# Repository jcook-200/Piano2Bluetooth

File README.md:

# Piano2Bluetooth
A hardware and software project to let a digital piano connect to Bluetooth headphones.

## Scructure

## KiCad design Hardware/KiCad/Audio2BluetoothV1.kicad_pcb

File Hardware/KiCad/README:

These are the kicad design files

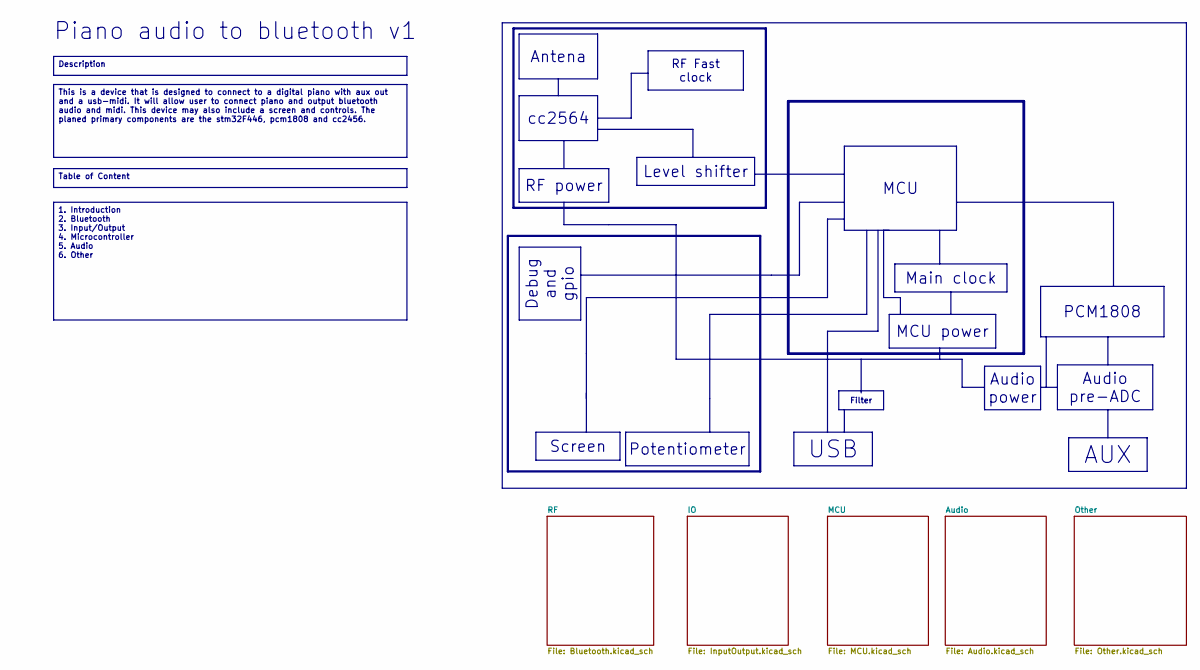
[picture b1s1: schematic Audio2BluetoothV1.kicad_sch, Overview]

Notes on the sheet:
Piano audio to bluetooth v1
Audio pre-ADC
Screen
Description
Debug and gpio
USB
Level shifter
RF Fast clock
Audio power
RF power
AUX
This is a device that is designed to connect to a digital piano with aux out and a usb-midi. It will allow user to connect piano and output bluetooth audio and midi. This device may also include a screen and controls. The planed primary components are the stm32F446, pcm1808 and cc2456.
1. Introduction 2. Bluetooth 3. Input/Output 4. Microcontroller 5. Audio 6. Other
Filter
MCU power
Potentiometer
MCU
Main clock
PCM1808
Table of Content
Antena
cc2564

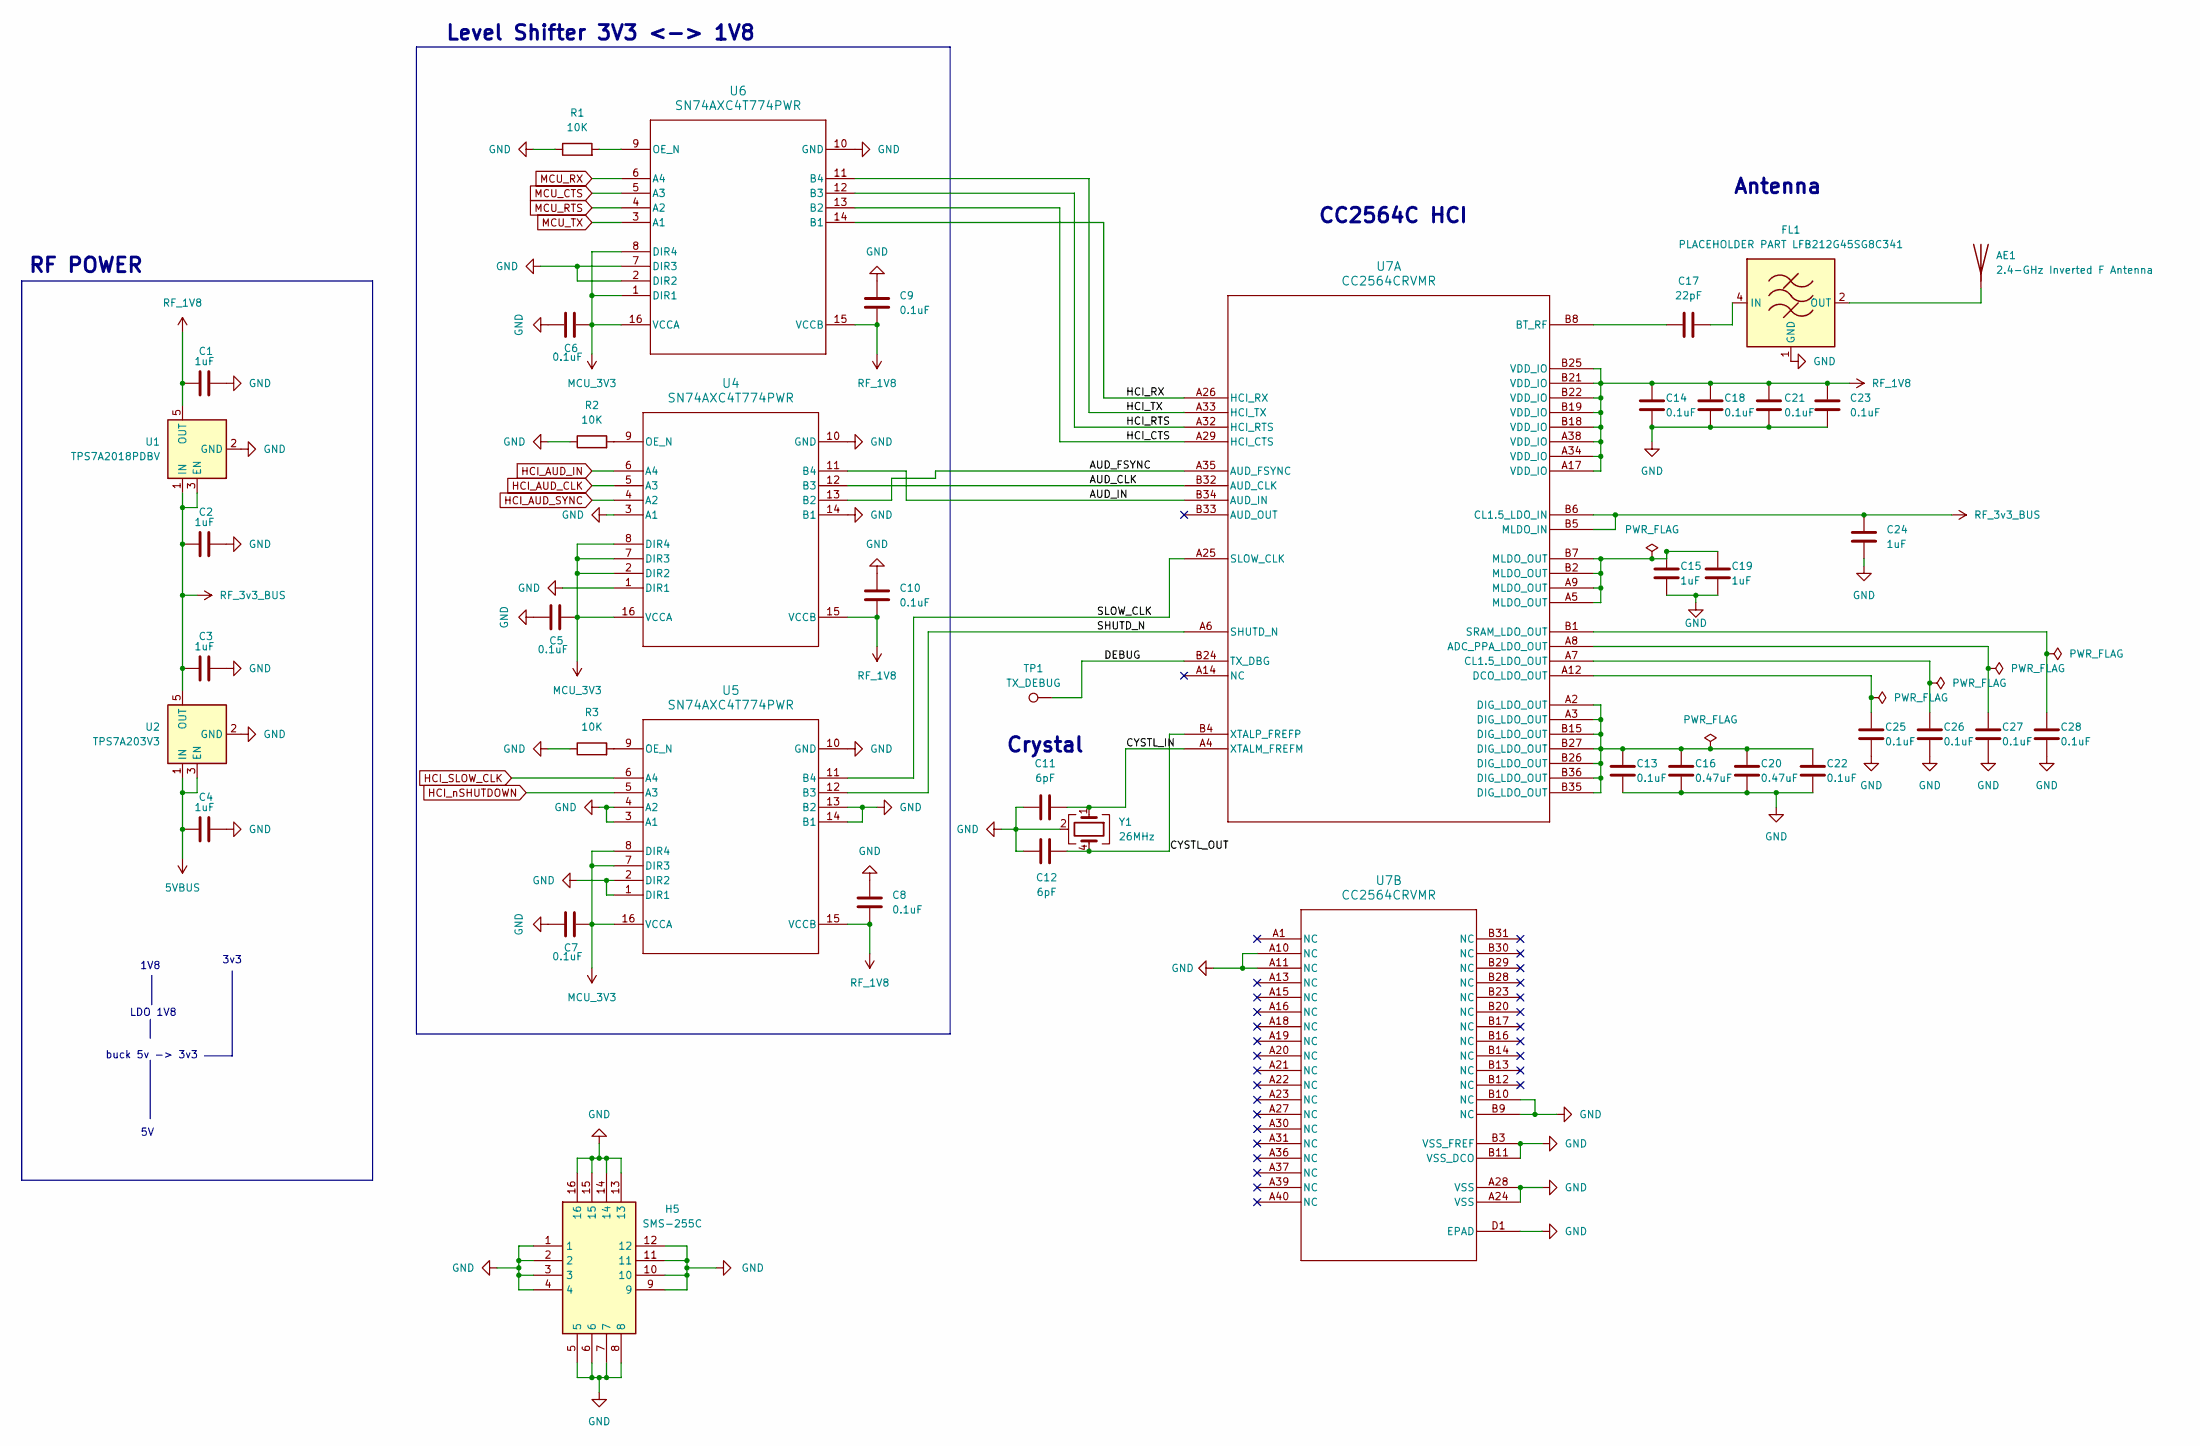
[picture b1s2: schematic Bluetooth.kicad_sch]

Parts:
AE1: 2.4-GHz Inverted F Antenna; Inverted F Antenna
C1, C2, C3, C4, C24: 1uF; C_0603_1608Metric_Pad1.08x0.95mm_HandSolder
C5, C6, C7, C8, C9, C10, C13, C14, C18, C21, C22, C23, C25, C26, C27, C28: 0.1uF; C_0402_1005Metric_Pad0.74x0.62mm_HandSolder
C11, C12: 6pF; C_0402_1005Metric_Pad0.74x0.62mm_HandSolder
C15, C19: 1uF; C_0402_1005Metric_Pad0.74x0.62mm_HandSolder
C16, C20: 0.47uF; C_0402_1005Metric_Pad0.74x0.62mm_HandSolder
C17: 22pF; C_0402_1005Metric_Pad0.74x0.62mm_HandSolder
FL1: PLACEHOLDER PART LFB212G45SG8C341; LFB212G45SG8C341
H5: SMS-255C; 36903205S; Mouser Part Number 710-36903205S
R1, R2, R3: 10K; R_0603_1608Metric_Pad0.98x0.95mm_HandSolder
TP1: TX_DEBUG; TestPoint_Pad_1.0x1.0mm
U1: TPS7A2018PDBV; SOT-23-5
U2: TPS7A203V3; SOT-23-5
U4, U5, U6: SN74AXC4T774PWR; PW0016A_N
U7: CC2564CRVMR; RVM0076A
Y1: 26MHz; ECS260836B2CKMTR

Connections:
5VBUS: C4.2, U2.1 (IN), U2.3 (EN); also elsewhere on the board
/RF/AUD_CLK: U4.12 (B3), U7.B32 (AUD_CLK)
/RF/AUD_FSYNC: U4.13 (B2), U7.A35 (AUD_FSYNC)
/RF/AUD_IN: U4.11 (B4), U7.B34 (AUD_IN)
/RF/CYSTL_IN: C11.2, U7.A4 (XTALM_FREFM), Y1.1
/RF/CYSTL_OUT: C12.2, U7.B4 (XTALP_FREFP), Y1.4
/RF/DEBUG: TP1.1 (1_1), U7.B24 (TX_DBG)
/RF/HCI_CTS: U6.13 (B2), U7.A29 (HCI_CTS)
/RF/HCI_RTS: U6.12 (B3), U7.A32 (HCI_RTS)
/RF/HCI_RX: U6.14 (B1), U7.A26 (HCI_RX)
/RF/HCI_TX: U6.11 (B4), U7.A33 (HCI_TX)
/RF/SHUTD_N: U5.12 (B3), U7.A6 (SHUTD_N)
/RF/SLOW_CLK: U5.11 (B4), U7.A25 (SLOW_CLK)
GND: C1.1, C2.1, C3.1, C4.1, C5.1, C6.1, C7.1, C8.1, C9.1, C10.1, C11.1, C12.1, C13.2, C14.2, C15.2, C16.2, C18.2, C19.2, C20.2, C21.2, C22.2, C23.2, C24.2, C25.2, C26.2, C27.2, C28.2, FL1.1 (GND), FL1.3 (GND), H5.1, H5.2, H5.3, H5.4, H5.5, H5.6, H5.7, H5.8, H5.9, H5.10, H5.11, H5.12, H5.13, H5.14, H5.15, H5.16, R1.1, R2.1, R3.1, U1.2 (GND), U2.2 (GND), U4.1 (DIR1), U4.3 (A1), U4.10 (GND), U4.14 (B1), U5.1 (DIR1), U5.2 (DIR2), U5.3 (A1), U5.4 (A2), U5.10 (GND), U5.13 (B2), U5.14 (B1), U6.2 (DIR2), U6.7 (DIR3), U6.10 (GND), U7.A10 (NC), U7.A11 (NC), U7.A24 (VSS), U7.A28 (VSS), U7.B3 (VSS_FREF), U7.B9 (NC), U7.B10 (NC), U7.B11 (VSS_DCO), U7.D1 (EPAD), Y1.2 (G), Y1.3 (G); also elsewhere on the board
HCI_AUD_CLK: U4.5 (A3); also elsewhere on the board
HCI_AUD_IN: U4.6 (A4); also elsewhere on the board
HCI_AUD_SYNC: U4.4 (A2); also elsewhere on the board
HCI_SLOW_CLK: U5.6 (A4); also elsewhere on the board
HCI_nSHUTDOWN: U5.5 (A3); also elsewhere on the board
MCU_3V3: C5.2, C6.2, C7.2, U4.2 (DIR2), U4.7 (DIR3), U4.8 (DIR4), U4.16 (VCCA), U5.7 (DIR3), U5.8 (DIR4), U5.16 (VCCA), U6.1 (DIR1), U6.8 (DIR4), U6.16 (VCCA); also elsewhere on the board
MCU_CTS: U6.5 (A3); also elsewhere on the board
MCU_RTS: U6.4 (A2); also elsewhere on the board
MCU_RX: U6.6 (A4); also elsewhere on the board
MCU_TX: U6.3 (A1); also elsewhere on the board
unnamed: AE1.1, FL1.2 (OUT)
unnamed: C13.1, C16.1, C20.1, C22.1, U7.A2 (DIG_LDO_OUT), U7.A3 (DIG_LDO_OUT), U7.B15 (DIG_LDO_OUT), U7.B26 (DIG_LDO_OUT), U7.B27 (DIG_LDO_OUT), U7.B35 (DIG_LDO_OUT), U7.B36 (DIG_LDO_OUT)
unnamed: C15.1, C19.1, U7.A5 (MLDO_OUT), U7.A9 (MLDO_OUT), U7.B2 (MLDO_OUT), U7.B7 (MLDO_OUT)
unnamed: C17.2, FL1.4 (IN)
unnamed: R2.2, U4.9 (OE_N)
unnamed: R3.2, U5.9 (OE_N)
unnamed: R1.2, U6.9 (OE_N)
unnamed: C27.1, U7.A8 (ADC_PPA_LDO_OUT)
unnamed: C17.1, U7.B8 (BT_RF)
unnamed: C26.1, U7.A7 (CL1.5_LDO_OUT)
unnamed: C25.1, U7.A12 (DCO_LDO_OUT)
unnamed: C28.1, U7.B1 (SRAM_LDO_OUT)
RF_1V8: C1.2, C8.2, C9.2, C10.2, C14.1, C18.1, C21.1, C23.1, U1.5 (OUT), U4.15 (VCCB), U5.15 (VCCB), U6.15 (VCCB), U7.A17 (VDD_IO), U7.A34 (VDD_IO), U7.A38 (VDD_IO), U7.B18 (VDD_IO), U7.B19 (VDD_IO), U7.B21 (VDD_IO), U7.B22 (VDD_IO), U7.B25 (VDD_IO)
RF_3v3_BUS: C2.2, C3.2, C24.1, U1.1 (IN), U1.3 (EN), U2.5 (OUT), U7.B5 (MLDO_IN), U7.B6 (CL1.5_LDO_IN)

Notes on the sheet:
LDO 1V8
Antenna
CC2564C HCI
Level Shifter 3V3 <-> 1V8
Crystal
1V8
RF POWER
3v3
buck 5v -> 3v3

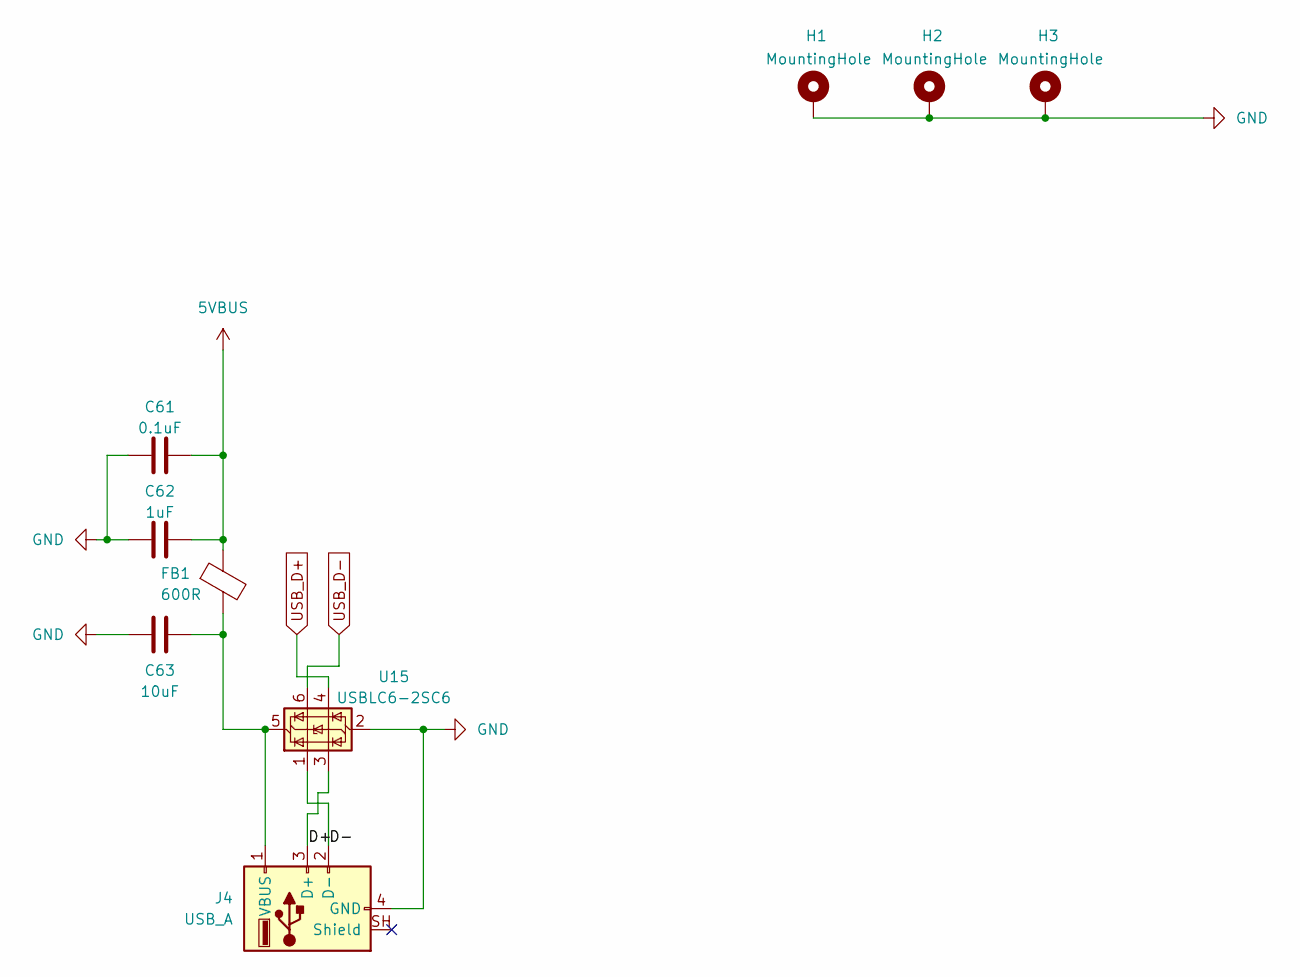
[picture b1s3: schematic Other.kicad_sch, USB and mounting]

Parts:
C61: 0.1uF; C_0603_1608Metric_Pad1.08x0.95mm_HandSolder
C62: 1uF; C_0603_1608Metric_Pad1.08x0.95mm_HandSolder
C63: 10uF; C_0805_2012Metric_Pad1.18x1.45mm_HandSolder
FB1: 600R; L_0603_1608Metric_Pad1.05x0.95mm_HandSolder
H1, H2, H3: MountingHole; MountingHole_3.2mm_M3_DIN965_Pad
J4: USB_A; USB_A_Molex_67643_Horizontal
U15: USBLC6-2SC6; SOT-23-6

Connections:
5VBUS: C61.2, C62.2, FB1.1; also elsewhere on the board
/Other/D+: J4.3 (D+), U15.3 (I/O2)
/Other/D-: J4.2 (D-), U15.1 (I/O1)
GND: C61.1, C62.1, C63.1, H1.1 (1_1), H2.1 (1_1), H3.1 (1_1), J4.4 (GND), U15.2 (GND); also elsewhere on the board
unnamed: C63.2, FB1.2, J4.1 (VBUS), U15.5 (VBUS)
USB_D+: U15.4 (I/O2); also elsewhere on the board
USB_D-: U15.6 (I/O1); also elsewhere on the board

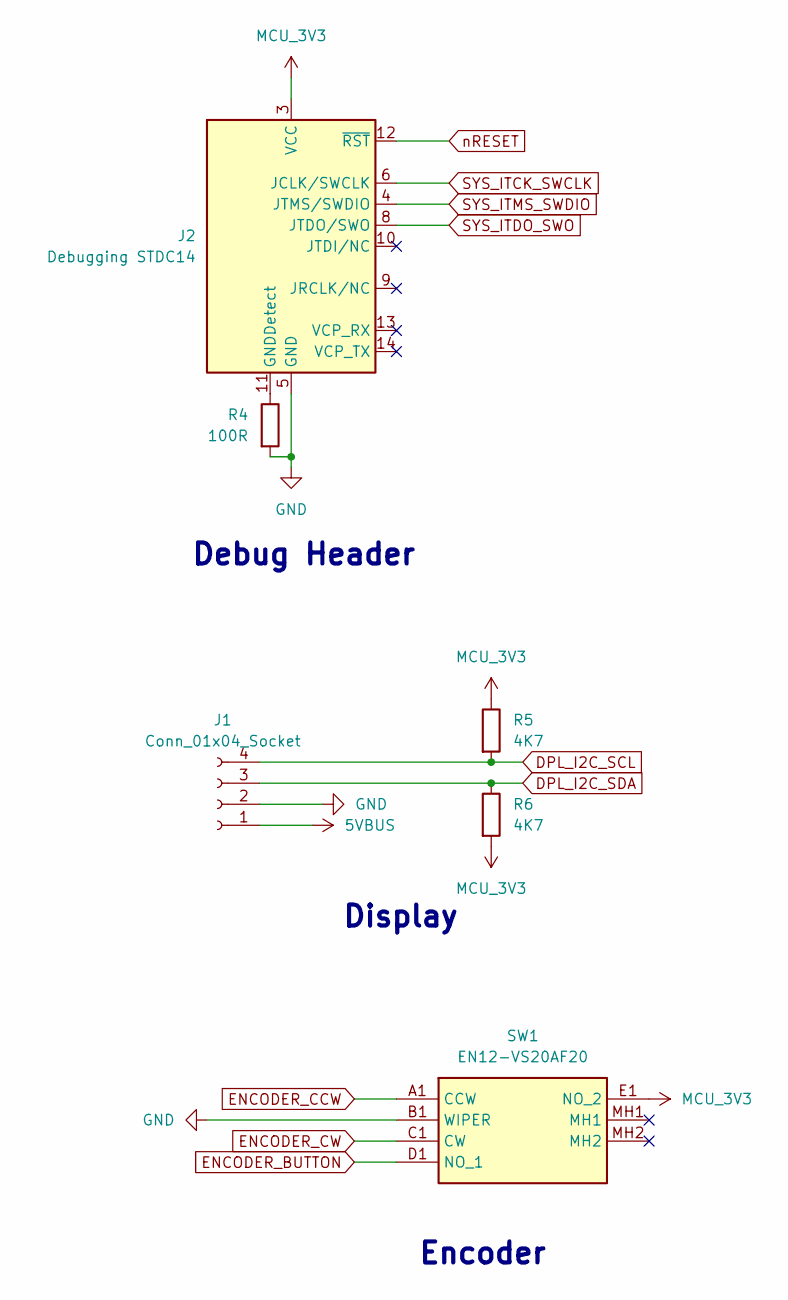
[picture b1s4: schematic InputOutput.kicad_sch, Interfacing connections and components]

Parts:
J1: Conn_01x04_Socket; PinHeader_1x04_P2.54mm_Vertical
J2: Debugging STDC14; PinHeader_2x07_P1.27mm_Vertical
R4: 100R; R_0603_1608Metric_Pad0.98x0.95mm_HandSolder
R5, R6: 4K7; R_0603_1608Metric_Pad0.98x0.95mm_HandSolder
SW1: EN12-VS20AF20; EN12VS20AF20; Mouser Part Number 858-EN12VS20AF20

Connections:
5VBUS: J1.1; also elsewhere on the board
DPL_I2C_SCL: J1.4, R5.2; also elsewhere on the board
DPL_I2C_SDA: J1.3, R6.1; also elsewhere on the board
ENCODER_BUTTON: SW1.D1 (NO_1); also elsewhere on the board
ENCODER_CCW: SW1.A1 (CCW); also elsewhere on the board
ENCODER_CW: SW1.C1 (CW); also elsewhere on the board
GND: J1.2, J2.5 (GND), J2.7 (GND), R4.2, SW1.B1 (WIPER); also elsewhere on the board
MCU_3V3: J2.3 (VCC), R5.1, R6.2, SW1.E1 (NO_2); also elsewhere on the board
unnamed: J2.11 (GNDDetect), R4.1
SYS_ITCK_SWCLK: J2.6 (JCLK/SWCLK); also elsewhere on the board
SYS_ITDO_SWO: J2.8 (JTDO/SWO); also elsewhere on the board
SYS_ITMS_SWDIO: J2.4 (JTMS/SWDIO); also elsewhere on the board
nRESET: J2.12 (~RST); also elsewhere on the board

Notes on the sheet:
Debug Header
Encoder
Display

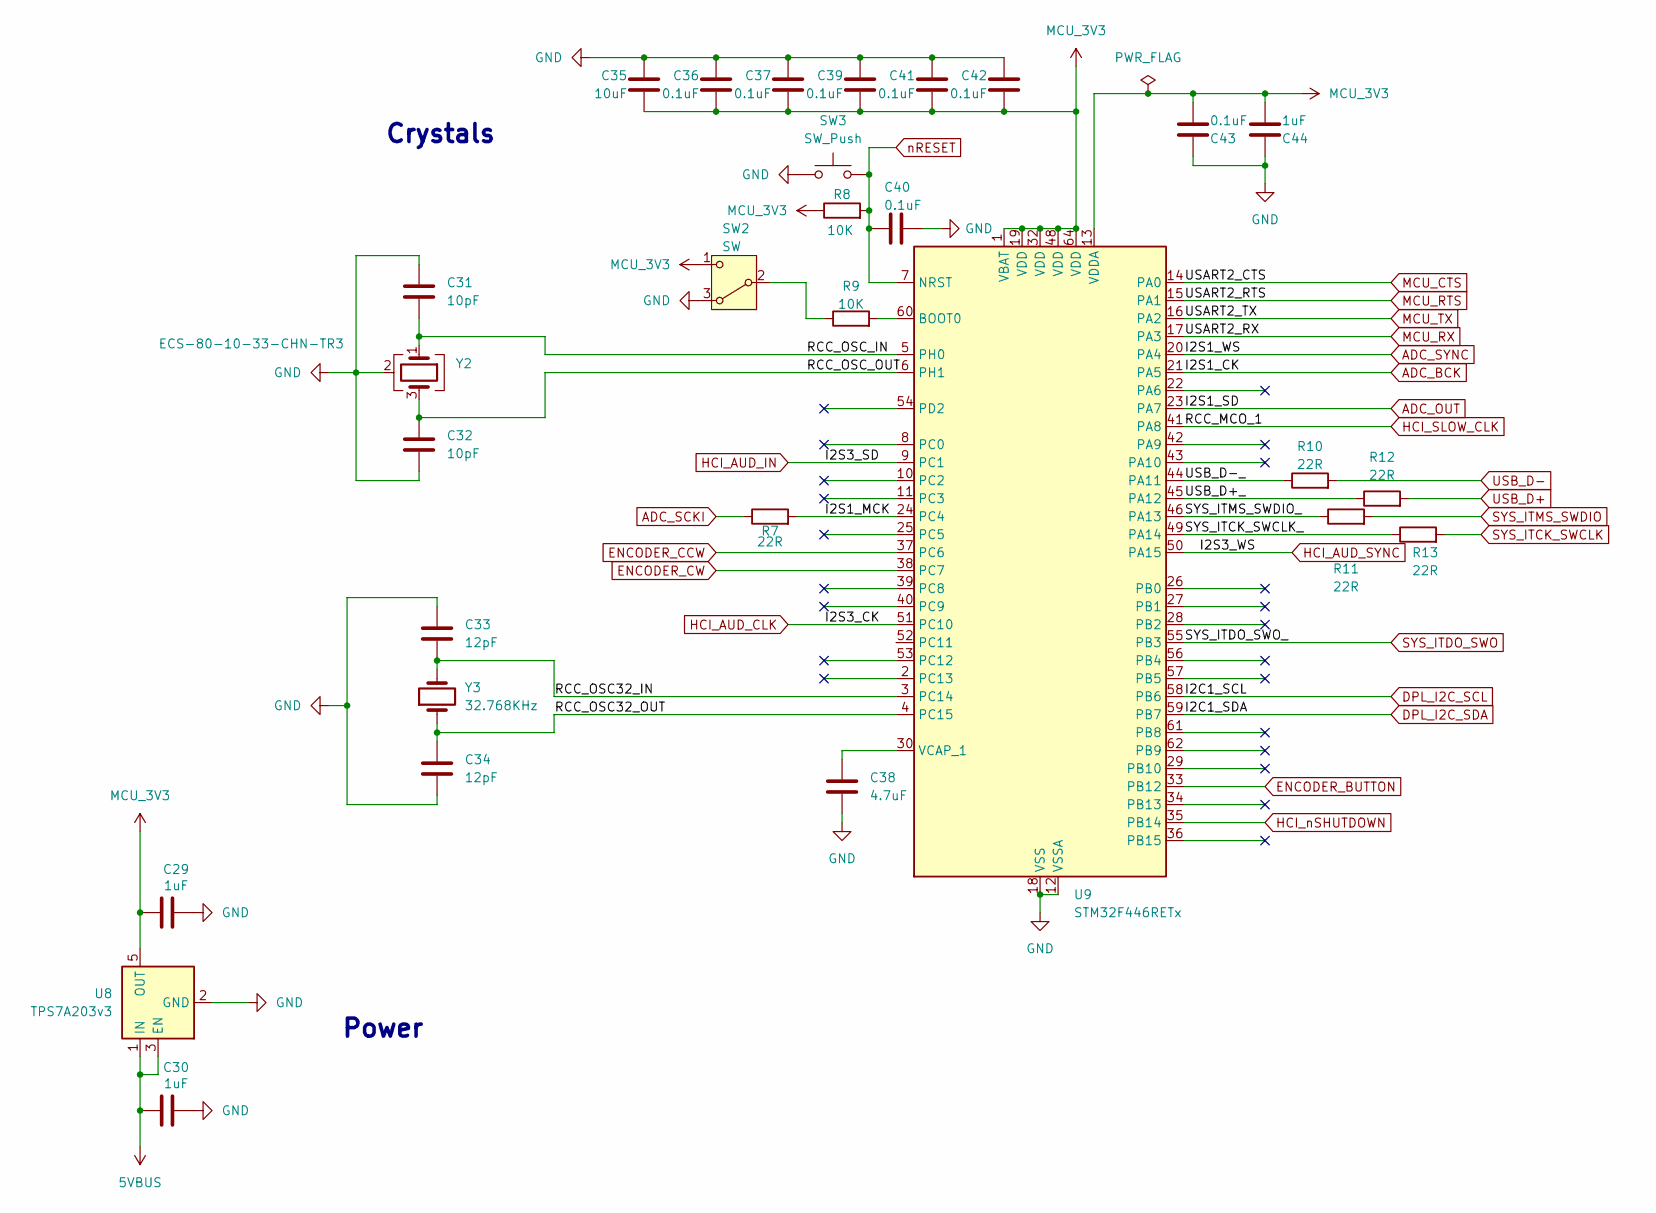
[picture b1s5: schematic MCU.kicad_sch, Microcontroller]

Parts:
C29, C30, C44: 1uF; C_0603_1608Metric_Pad1.08x0.95mm_HandSolder
C31, C32: 10pF; C_0402_1005Metric_Pad0.74x0.62mm_HandSolder
C33, C34: 12pF; C_0402_1005Metric_Pad0.74x0.62mm_HandSolder
C35: 10uF; C_0805_2012Metric_Pad1.18x1.45mm_HandSolder
C36, C37, C39, C40, C41, C42, C43: 0.1uF; C_0402_1005Metric_Pad0.74x0.62mm_HandSolder
C38: 4.7uF; C_0603_1608Metric_Pad1.08x0.95mm_HandSolder
R7, R10, R11, R12, R13: 22R; R_0603_1608Metric_Pad0.98x0.95mm_HandSolder
R8, R9: 10K; R_0603_1608Metric_Pad0.98x0.95mm_HandSolder
SW2: SW; SW_SPDT_PCM12
SW3: SW_Push; SW_PUSH_6mm_H5mm
U8: TPS7A203v3; SOT-23-5
U9: STM32F446RETx; LQFP-64_10x10mm_P0.5mm
Y2: ECS-80-10-33-CHN-TR3; ECS801033CHNTR3
Y3: 32.768KHz; ECS327734BTR

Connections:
5VBUS: C30.1, U8.1 (IN), U8.3 (EN); also elsewhere on the board
/MCU/I2S1_MCK: R7.2, U9.24 (PC4)
/MCU/RCC_OSC32_IN: C33.2, U9.3 (PC14), Y3.2
/MCU/RCC_OSC32_OUT: C34.1, U9.4 (PC15), Y3.1
/MCU/RCC_OSC_IN: C31.2, U9.5 (PH0), Y2.1
/MCU/RCC_OSC_OUT: C32.1, U9.6 (PH1), Y2.3
/MCU/SYS_ITCK_SWCLK_: R13.1, U9.49 (PA14)
/MCU/SYS_ITMS_SWDIO_: R11.1, U9.46 (PA13)
/MCU/USB_D+_: R12.1, U9.45 (PA12)
/MCU/USB_D-_: R10.1, U9.44 (PA11)
ADC_BCK: U9.21 (PA5); also elsewhere on the board
ADC_OUT: U9.23 (PA7); also elsewhere on the board
ADC_SCKI: R7.1; also elsewhere on the board
ADC_SYNC: U9.20 (PA4); also elsewhere on the board
DPL_I2C_SCL: U9.58 (PB6); also elsewhere on the board
DPL_I2C_SDA: U9.59 (PB7); also elsewhere on the board
ENCODER_BUTTON: U9.33 (PB12); also elsewhere on the board
ENCODER_CCW: U9.37 (PC6); also elsewhere on the board
ENCODER_CW: U9.38 (PC7); also elsewhere on the board
GND: C29.2, C30.2, C31.1, C32.2, C33.1, C34.2, C35.1, C36.1, C37.1, C38.2, C39.1, C40.1, C41.1, C42.1, C43.1, C44.1, SW2.3 (A), SW3.1, U8.2 (GND), U9.12 (VSSA), U9.18 (VSS), U9.31 (VSS), U9.47 (VSS), U9.63 (VSS), Y2.2 (G), Y2.4 (G); also elsewhere on the board
HCI_AUD_CLK: U9.51 (PC10); also elsewhere on the board
HCI_AUD_IN: U9.9 (PC1); also elsewhere on the board
HCI_AUD_SYNC: U9.50 (PA15); also elsewhere on the board
HCI_SLOW_CLK: U9.41 (PA8); also elsewhere on the board
HCI_nSHUTDOWN: U9.35 (PB14); also elsewhere on the board
MCU_3V3: C29.1, C35.2, C36.2, C37.2, C39.2, C41.2, C42.2, C43.2, C44.2, R8.1, SW2.1 (C), U8.5 (OUT), U9.1 (VBAT), U9.13 (VDDA), U9.19 (VDD), U9.32 (VDD), U9.48 (VDD), U9.64 (VDD); also elsewhere on the board
MCU_CTS: U9.14 (PA0); also elsewhere on the board
MCU_RTS: U9.15 (PA1); also elsewhere on the board
MCU_RX: U9.17 (PA3); also elsewhere on the board
MCU_TX: U9.16 (PA2); also elsewhere on the board
unnamed: R9.1, SW2.2 (B)
unnamed: R9.2, U9.60 (BOOT0)
unnamed: C38.1, U9.30 (VCAP_1)
SYS_ITCK_SWCLK: R13.2; also elsewhere on the board
SYS_ITDO_SWO: U9.55 (PB3); also elsewhere on the board
SYS_ITMS_SWDIO: R11.2; also elsewhere on the board
USB_D+: R12.2; also elsewhere on the board
USB_D-: R10.2; also elsewhere on the board
nRESET: C40.2, R8.2, SW3.2, U9.7 (NRST); also elsewhere on the board

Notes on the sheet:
Crystals
Power

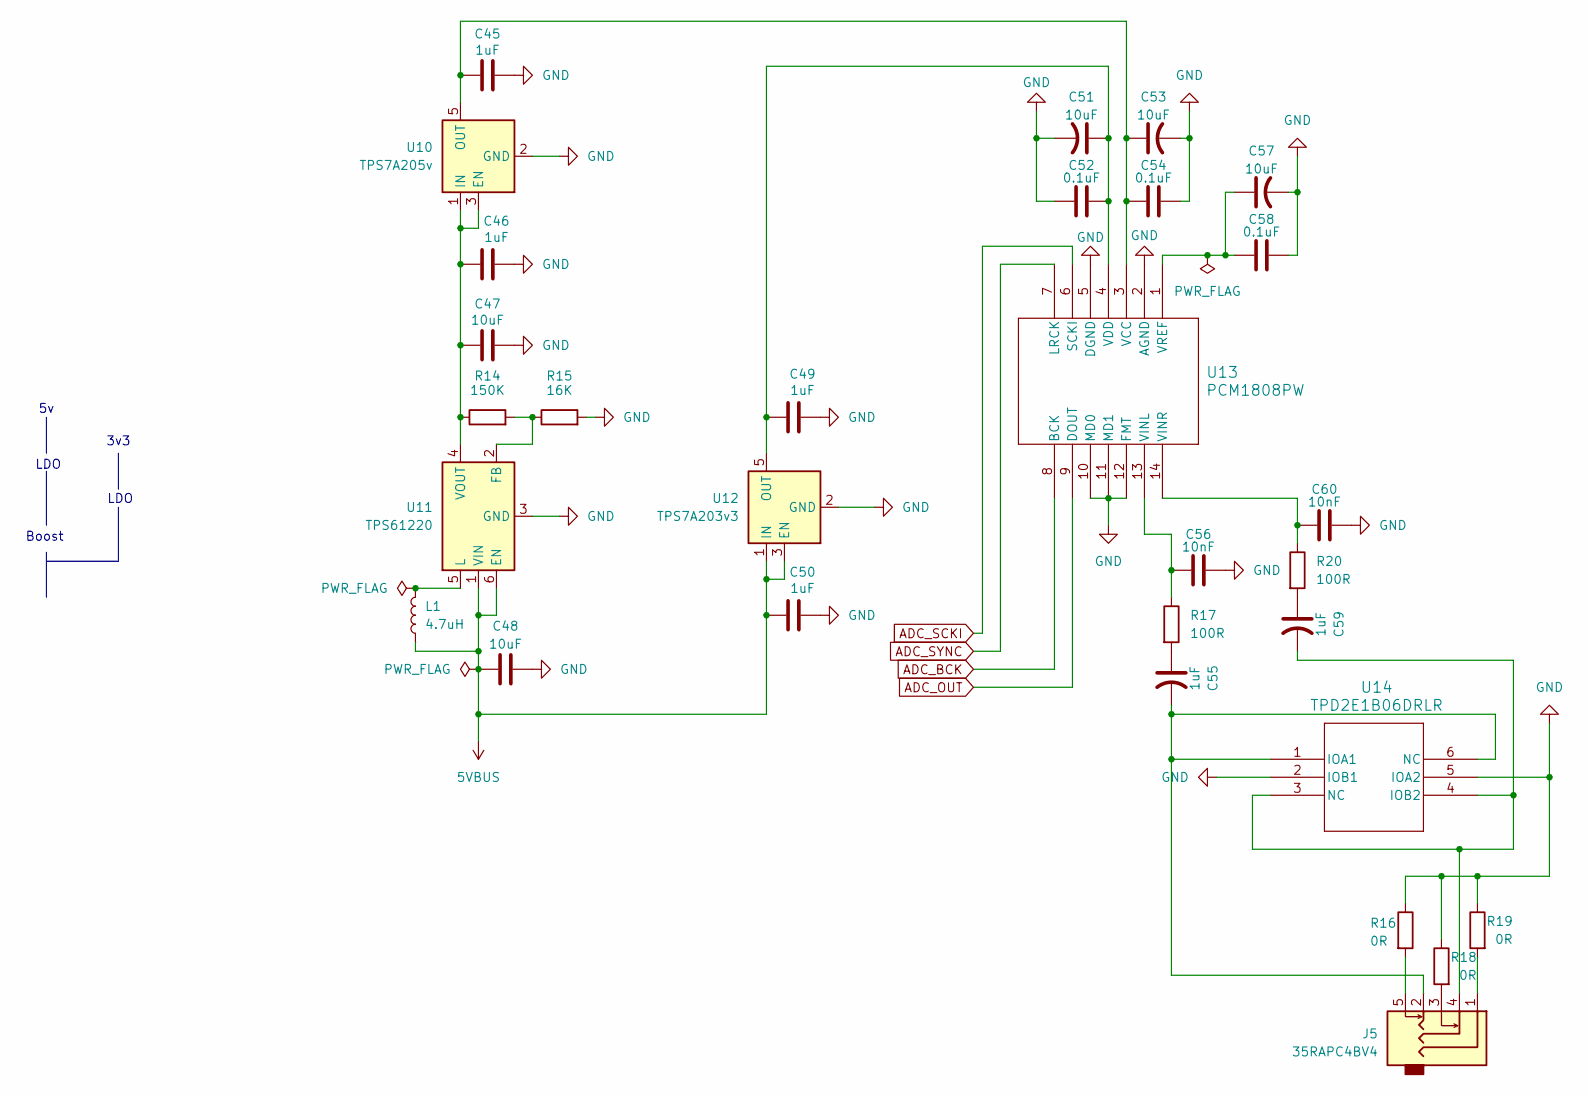
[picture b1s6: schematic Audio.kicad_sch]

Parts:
C45, C46, C49, C50: 1uF; C_0603_1608Metric_Pad1.08x0.95mm_HandSolder
C47, C48, C57: 10uF; C_0805_2012Metric_Pad1.18x1.45mm_HandSolder
C51, C53: 10uF; C_1206_3216Metric_Pad1.33x1.80mm_HandSolder
C52, C54, C58: 0.1uF; C_0402_1005Metric_Pad0.74x0.62mm_HandSolder
C55, C59: 1uF; C_Rect_L7.2mm_W5.5mm_P5.00mm_FKS2_FKP2_MKS2_MKP2
C56, C60: 10nF; C_0603_1608Metric_Pad1.08x0.95mm_HandSolder
J5: 35RAPC4BV4
L1: 4.7uH; L_Coilcraft_XFL2010
R14: 150K; R_0603_1608Metric_Pad0.98x0.95mm_HandSolder
R15: 16K; R_0603_1608Metric_Pad0.98x0.95mm_HandSolder
R16, R18, R19: 0R; C_0603_1608Metric_Pad1.08x0.95mm_HandSolder
R17, R20: 100R; R_0603_1608Metric_Pad0.98x0.95mm_HandSolder
U10: TPS7A205v; SOT-23-5
U11: TPS61220; Texas_R-PDSO-G6
U12: TPS7A203v3; SOT-23-5
U13: PCM1808PW; PW14-L
U14: TPD2E1B06DRLR; DRL6_TEX-L

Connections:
5VBUS: C48.1, C50.1, L1.1, U11.1 (VIN), U11.6 (EN), U12.1 (IN), U12.3 (EN); also elsewhere on the board
ADC_BCK: U13.8 (BCK); also elsewhere on the board
ADC_OUT: U13.9 (DOUT); also elsewhere on the board
ADC_SCKI: U13.6 (SCKI); also elsewhere on the board
ADC_SYNC: U13.7 (LRCK); also elsewhere on the board
GND: C45.2, C46.2, C47.2, C48.2, C49.2, C50.2, C51.2, C52.1, C53.2, C54.1, C56.1, C57.2, C58.1, C60.1, R15.2, R16.1, R18.1, R19.1, U10.2 (GND), U11.3 (GND), U12.2 (GND), U13.2 (AGND), U13.5 (DGND), U13.10 (MD0), U13.11 (MD1), U13.12 (FMT), U14.2 (IOB1), U14.5 (IOA2); also elsewhere on the board
unnamed: C55.1, R17.2
unnamed: C59.1, R20.2
unnamed: J5.1, R19.2
unnamed: J5.3, R18.2
unnamed: J5.5, R16.2
unnamed: C46.1, C47.1, R14.1, U10.1 (IN), U10.3 (EN), U11.4 (VOUT)
unnamed: C45.1, C53.1, C54.2, U10.5 (OUT), U13.3 (VCC)
unnamed: R14.2, R15.1, U11.2 (FB)
unnamed: L1.2, U11.5 (L)
unnamed: C49.1, C51.1, C52.2, U12.5 (OUT), U13.4 (VDD)
unnamed: C56.2, R17.1, U13.13 (VINL)
unnamed: C60.2, R20.1, U13.14 (VINR)
unnamed: C57.1, C58.2, U13.1 (VREF)
unnamed: C55.2, J5.2, U14.1 (IOA1), U14.6 (NC)
unnamed: C59.2, J5.4, U14.3 (NC), U14.4 (IOB2)

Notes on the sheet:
3v3
Boost
LDO

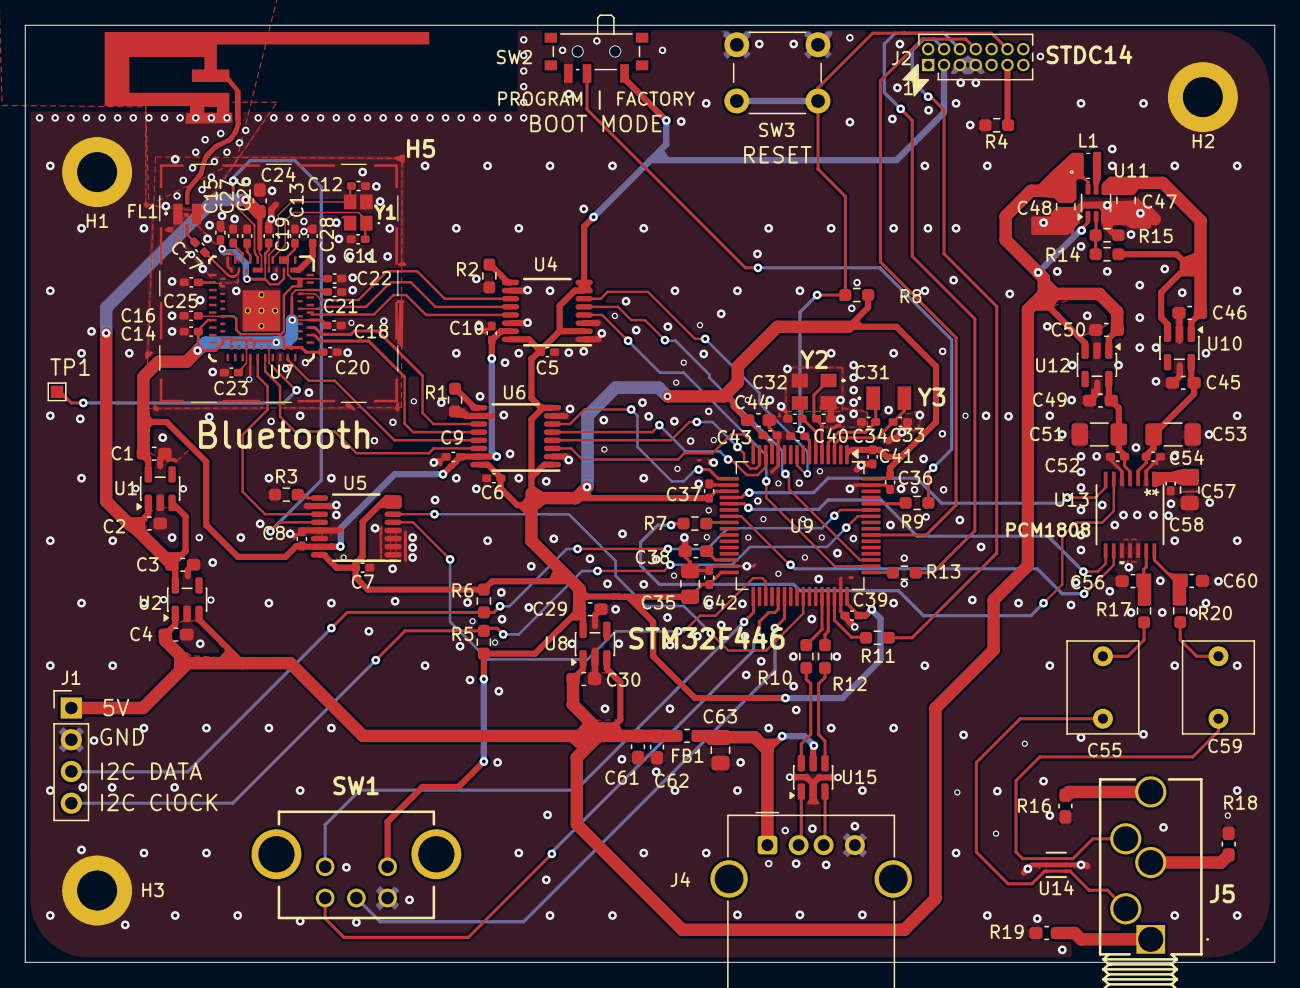
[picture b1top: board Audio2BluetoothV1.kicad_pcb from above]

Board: 4 copper layers, 100.0 x 75.0 mm, 116 parts (0 on the bottom side), 83 nets.

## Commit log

2026-05-23 Update README.md
    Added a design needs section
2026-05-23 Update README.md
    Edited formatting and added a hardware section
2026-05-23 Create README.md
    created hardware folder
2026-05-23 Update README.md
    formatting
2026-05-23 Update README.md
    Added to the ADC selection
2026-05-23 Update README.md
    capitalize Bluetooth
2026-05-23 Update README.md
    Added to Bluetooth chip selection
2026-05-23 Update README.md
    Started microcontroller section and added reflections
2026-05-23 Update README.md
    edited microcontroller section
2026-05-23 Add PDF schematic
    Schematic of the audio to Bluetooth PCB
2026-05-23 Added PCB pdf
2026-05-24 Rename Audio2BluetoothV1.pdf to Audio2BluetoothV1_Schematic.pdf
    Name change
2026-05-29 Update README.md
    Added a revisions section
2026-05-30 Update README.md
    Added to revisions
2026-06-06 Add files via upload
    Gerber Zip added
2026-06-15 Create README
    added kicad folder
2026-06-15 Add files via upload
    added kicad design files
